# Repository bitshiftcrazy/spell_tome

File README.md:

# Spell Tome PCB

A handheld fantasy-themed PCB spell tome designed for tabletop RPGs and other shenanigans.

The Spell Tome is a sandwiched, book-like PCB build consisting of
a functional electronics PCB and a decorative top PCB.
Originally it was designed as a magical artifact for a custom text adventure and small games.

Right now it's evolving into anything that can be done with a tiny OLED and 4 buttons (stay tuned!).

---

## Features

- Handheld layered PCB construction
- Decorative top PCB with silkscreen and copper artwork
- Book-label-style OLED display
- RGB status eye staring at your soul
- Push buttons
- Powered by 2x AAA batteries
- Designed around the Seeed Studio XIAO RP2040
- Custom firmware for text adventures and other games (currently under cleanup, coming soon)

---

## Gallery

---

## Hardware Overview

The Spell Tome is designed around a Seeed Studio XIAO RP2040 to make it easy to customise, reprogram, and repurpose. It consists of two separate PCBs that together form a small handheld device, no additional case needed.

### Bottom PCB

The bottom PCB holds all the electronics, meaning the schematics only refer to the bottom PCB. Buttons and RGB LED parts are flat so that the handheld stays slim overall.

### Top PCB

The top PCB functions as a decorative cover for the handheld. It has an eye-shaped keepout zone so the status LED's light shines through. Very magic. Much wow.

It also has cutouts for 4 3D printed buttons.

---

## Main Components

The parts selection is mainly influenced by "I have this at home already" and "I want people to be able to easily assemble and program it":

- Seeed Studio XIAO RP2040 microcontroller
- 1.3" OLED display
- MCP1640 boost converter
- RGB status LED
- 4x tactile push buttons
- Power slide switch
- 2x AAA battery holder
- 4x 3D printed button caps
- 4x spacers and screws (ideally golden, for the vibe)

Of course the project also uses standard components such as
resistors, capacitors, and passive power circuitry. You'll find them and their respective values in the BOM files in:

```text
fabrication/bom/
```

---

## Assembly

### PCB Stackup

Since the Spell Tome uses a layered PCB construction, you'll need to fit these parts together:

1. Bottom electronics PCB
2. Printed button elements
3. Decorative top PCB
4. Battery holder

To assemble the Tome you'll need M2.5 screws and spacers/standoffs (6 mm worked well for me here).

Detailed soldering instructions follow.

Assuming you already soldered the parts:

1. Screw the standoff to the bottom PCB (screw on the outward-facing side, standoff inside)
2. Put the button-shaped button parts through the top PCB's holes and secure them with the little 3D printed rings
3. Put the cover on top of the standoffs on the bottom PCB and test the buttons a little to find a good distance before screwing it on (you can also adjust this later with something pointy)
4. Glue the battery holder to the back where it feels comfortable and make sure to secure the wires with a little glue as well

#### Mechanical Button Parts

3D printable parts are available in:

```text
mechanical/
```

Print the buttons without supports.

### Assembly Notes

- you can find golden screws that pass the vibe check if you look for jewellery screws
- I printed the buttons in white PLA, but it's probably more comfy to use TPU and prettier with something shiny
- depending on how thick you want that thing to be, you can also use longer standoffs and put the batteries between the sandwich layers

---

## Repository Structure

```text
spell_tome/
├── artwork/        # Source artwork and SVG files
├── fabrication/    # BOMs and fabrication outputs
├── libraries/      # Local KiCad symbol and footprint libraries
├── mechanical/     # 3D printable parts
├── pics/           # Images and renders
├── *.kicad_*       # Main KiCad project files
└── README.md
```

---

## Firmware

Firmware was hacked together in one long weekend and is currently under cleanup (guess "a little messy" is fine for personal projects, "wtf even is that" is not ;)) and will be published in this repo soon.

Features:
- the cringiest text adventure you'll ever play
- impractical mini games
- the mysterious blood moon side quest

---

## Fabrication

Gerbers and manufacturing files can be generated directly from the KiCad project files. The current Gerbers are the tested and working version.

Please make sure to regenerate them before sending something to fabrication, I cannot be trusted to remember to do this after every change I make.

Pre-generated fabrication outputs belong and are available in:

```text
fabrication/gerbers/
```

---

## Color inspo

## Further Reading
- [Hackster: This Open Source RP2040 Development Board Looks Like a Magic Spellbook](https://www.hackster.io/news/this-open-source-rp2040-development-board-looks-like-a-magic-spellbook-52a614f74b81)

## License

Hardware design files are licensed under the CERN Open Hardware Licence
Version 2 - Strongly Reciprocal (CERN-OHL-S-2.0).

See the `LICENSE` file for details.

Copyright (c) 2026 miss.molerat

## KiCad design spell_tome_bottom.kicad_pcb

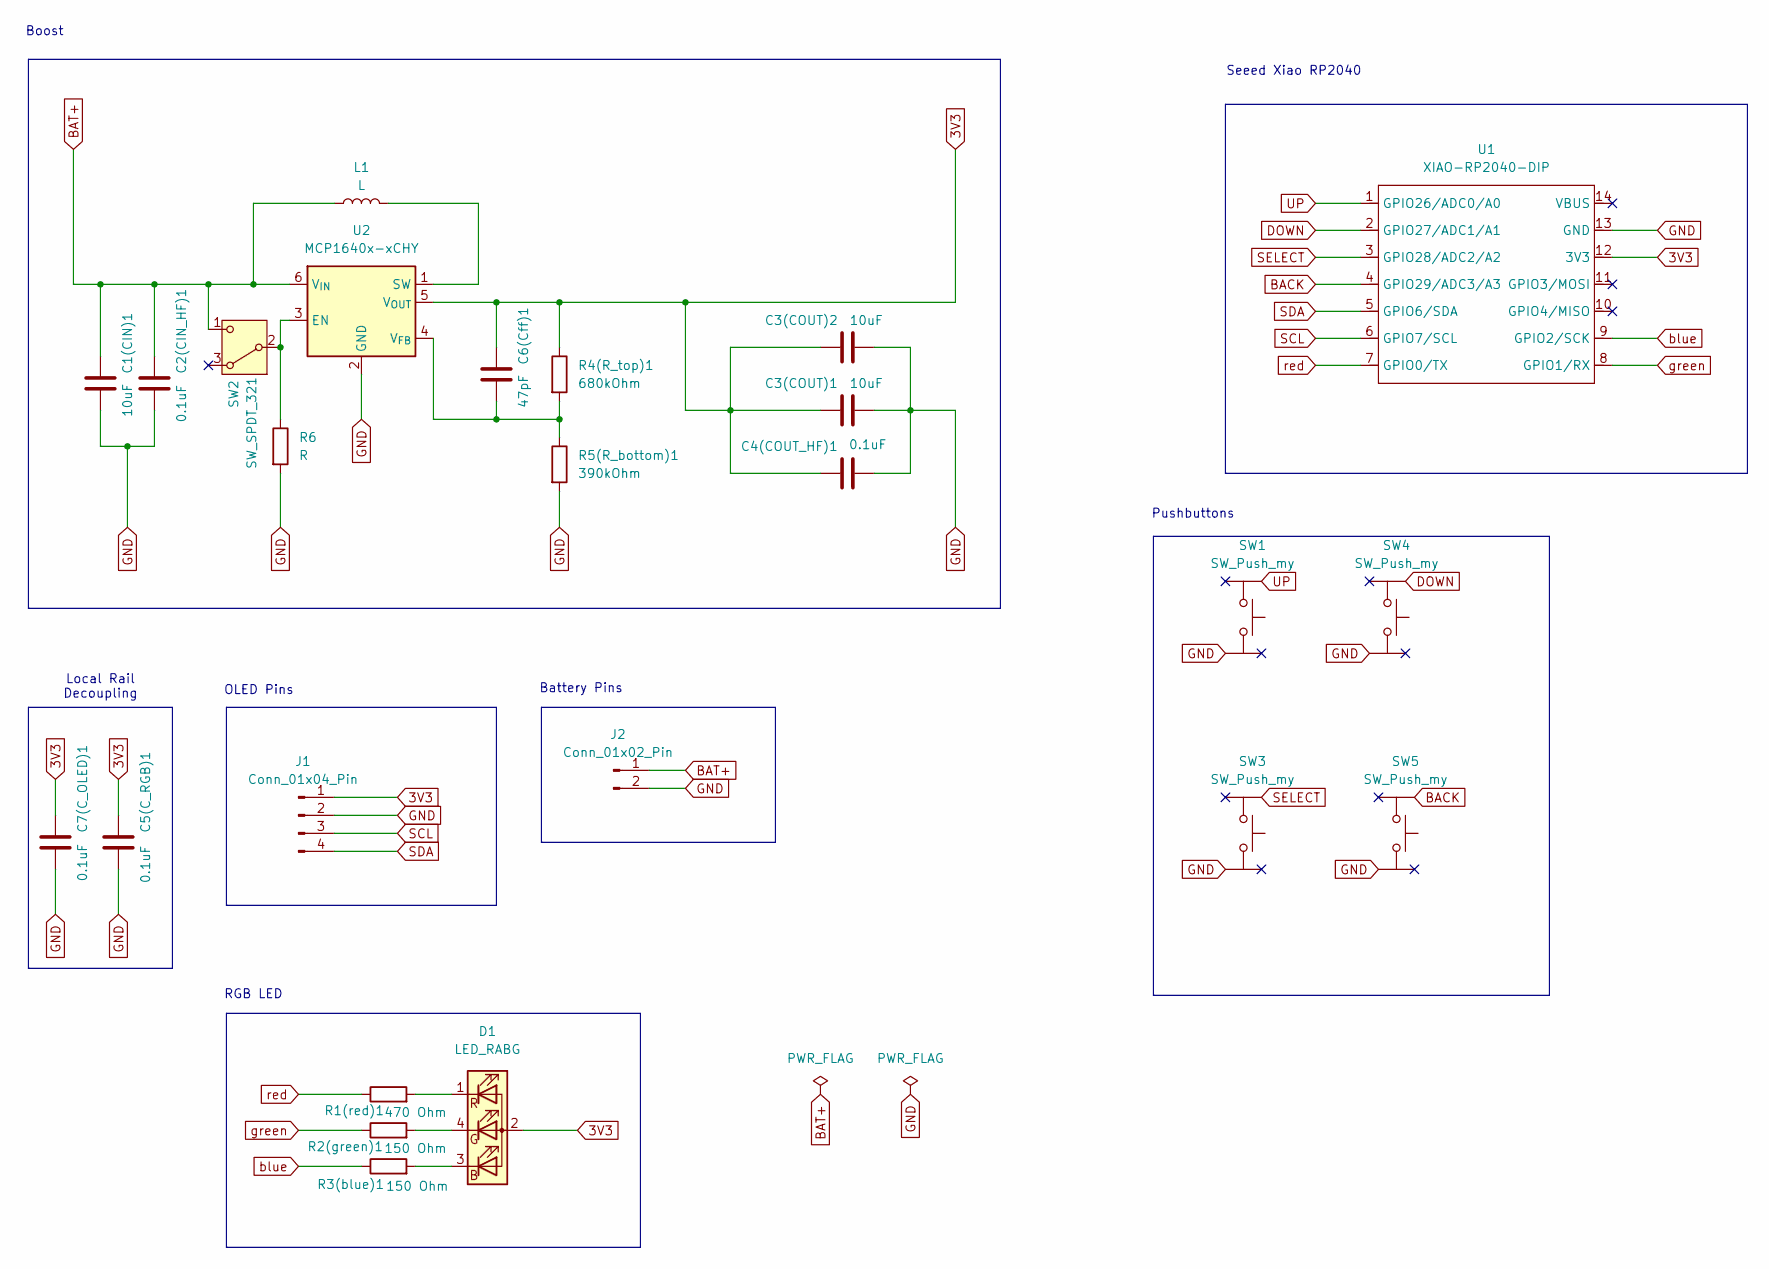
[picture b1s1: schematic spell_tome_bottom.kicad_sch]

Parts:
C1(CIN)1, C3(COUT)1, C3(COUT)2: 10uF; C_0805_2012Metric; LCSC C15850
C2(CIN_HF)1, C4(COUT_HF)1, C5(C_RGB)1, C7(C_OLED)1: 0.1uF; C_0603_1608Metric; LCSC C14663
C6(Cff)1: 47pF; C_0603_1608Metric; LCSC C94904
D1: LED_RABG; LED-ARRAY-SMD_4P-L1.6-W1.5-TL_NH-B1515RGBA; LCSC C2874115
J1: Conn_01x04_Pin; PinHeader_1x04_P2.54mm_Vertical
J2: Conn_01x02_Pin; PinHeader_1x02_P2.54mm_Vertical
L1: L; IND-SMD_L6.0-W6.0_NR6028T2R2N
R1(red)1: 470 Ohm; R_0603_1608Metric; LCSC C23179
R2(green)1, R3(blue)1: 150 Ohm; R_0603_1608Metric; LCSC C22808
R4(R_top)1: 680kOhm; R_0603_1608Metric; LCSC C25822
R5(R_bottom)1: 390kOhm; R_0603_1608Metric; LCSC C23150
R6: R; R_0603_1608Metric; LCSC C25803
SW1, SW3, SW4, SW5: SW_Push_my; SW-SMD_4P-L3.4-W3.4-P2.15-LS4.2; LCSC C596271
SW2: SW_SPDT_321; SW-SMD_SSSS810701; LCSC C97433
U1: XIAO-RP2040-DIP
U2: MCP1640x-xCHY; SOT-23-6_L2.9-W1.6-P0.95-LS2.8-BR; LCSC C44365

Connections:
3V3: C3(COUT)1.1, C3(COUT)2.1, C4(COUT_HF)1.1, C5(C_RGB)1.1, C6(Cff)1.1, C7(C_OLED)1.1, D1.2 (A), J1.1, R4(R_top)1.1, U1.12 (3V3), U2.5 (V_{OUT})
BACK: SW5.1, U1.4 (GPIO29/ADC3/A3)
BAT+: C1(CIN)1.1, C2(CIN_HF)1.1, J2.1, L1.1, SW2.1 (C), U2.6 (V_{IN})
DOWN: SW4.1, U1.2 (GPIO27/ADC1/A1)
GND: C1(CIN)1.2, C2(CIN_HF)1.2, C3(COUT)1.2, C3(COUT)2.2, C4(COUT_HF)1.2, C5(C_RGB)1.2, C7(C_OLED)1.2, J1.2, J2.2, R5(R_bottom)1.2, R6.2, SW1.4, SW3.4, SW4.4, SW5.4, U1.13 (GND), U2.2 (GND)
unnamed: D1.3 (BK), R3(blue)1.2
unnamed: D1.4 (GK), R2(green)1.2
unnamed: D1.1 (RK), R1(red)1.2
unnamed: R6.1, SW2.2 (B), U2.3 (EN)
unnamed: L1.2, U2.1 (SW)
unnamed: C6(Cff)1.2, R4(R_top)1.2, R5(R_bottom)1.1, U2.4 (V_{FB})
SCL: J1.3, U1.6 (GPIO7/SCL)
SDA: J1.4, U1.5 (GPIO6/SDA)
SELECT: SW3.1, U1.3 (GPIO28/ADC2/A2)
UP: SW1.1, U1.1 (GPIO26/ADC0/A0)
blue: R3(blue)1.1, U1.9 (GPIO2/SCK)
green: R2(green)1.1, U1.8 (GPIO1/RX)
red: R1(red)1.1, U1.7 (GPIO0/TX)

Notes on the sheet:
OLED Pins
RGB LED
Battery Pins
Pushbuttons
Boost
Seeed Xiao RP2040
Local Rail Decoupling

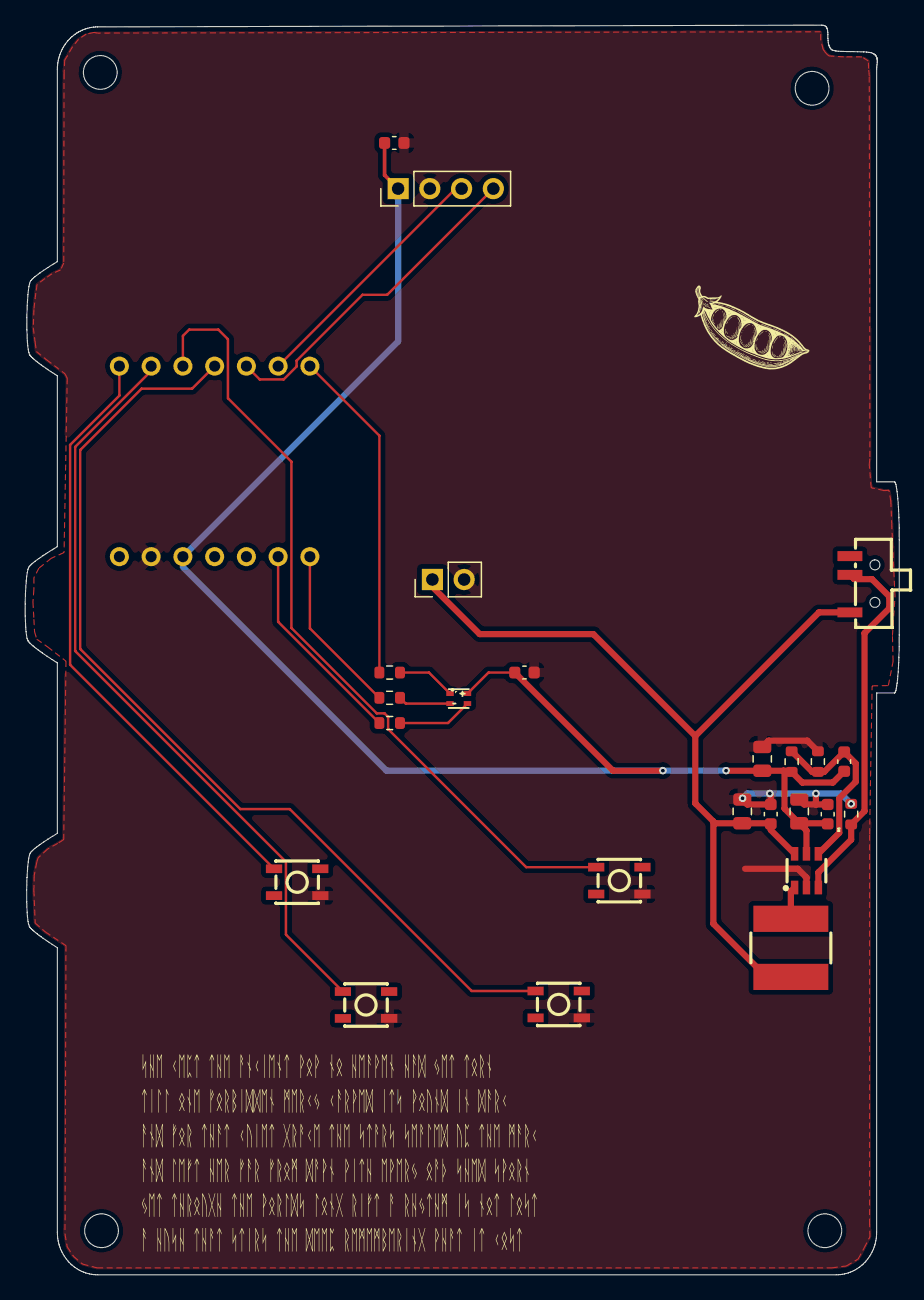
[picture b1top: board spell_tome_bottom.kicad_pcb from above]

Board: 2 copper layers, 69.9 x 99.9 mm, 25 parts (1 on the bottom side), 18 nets.

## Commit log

2026-05-26 initial spell tome open hardware release
